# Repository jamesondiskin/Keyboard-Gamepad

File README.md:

# Keyboard-Gamepad
 MX Switch based gamepad for fighting games

Added way too many submodules as for now I am unsure which parts library to use.

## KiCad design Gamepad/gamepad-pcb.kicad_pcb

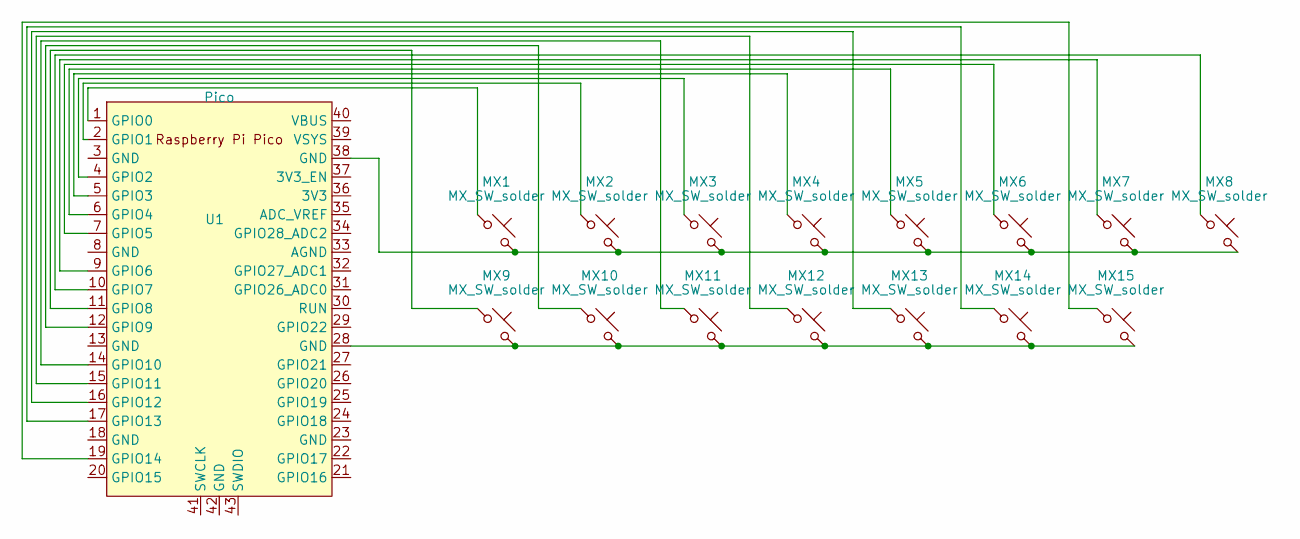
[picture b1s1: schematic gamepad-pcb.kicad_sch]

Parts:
MX1, MX2, MX3, MX4, MX5, MX6, MX7, MX8, MX9, MX10, MX11, MX12, MX13, MX14, MX15: MX_SW_solder; SW_MX_1u
U1: Pico; RPi_Pico_SMD_TH

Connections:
unnamed: MX1.2, MX2.2, MX3.2, MX4.2, MX5.2, MX6.2, MX7.2, MX8.2, U1.38 (GND)
unnamed: MX9.2, MX10.2, MX11.2, MX12.2, MX13.2, MX14.2, MX15.2, U1.28 (GND)
unnamed: MX1.1, U1.1 (GPIO0)
unnamed: MX2.1, U1.2 (GPIO1)
unnamed: MX3.1, U1.4 (GPIO2)
unnamed: MX4.1, U1.5 (GPIO3)
unnamed: MX5.1, U1.6 (GPIO4)
unnamed: MX6.1, U1.7 (GPIO5)
unnamed: MX7.1, U1.9 (GPIO6)
unnamed: MX8.1, U1.10 (GPIO7)
unnamed: MX9.1, U1.11 (GPIO8)
unnamed: MX10.1, U1.12 (GPIO9)
unnamed: MX11.1, U1.14 (GPIO10)
unnamed: MX12.1, U1.15 (GPIO11)
unnamed: MX13.1, U1.16 (GPIO12)
unnamed: MX14.1, U1.17 (GPIO13)
unnamed: MX15.1, U1.19 (GPIO14)

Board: 2 copper layers, 16 parts (0 on the bottom side), 17 nets, no tracks yet.

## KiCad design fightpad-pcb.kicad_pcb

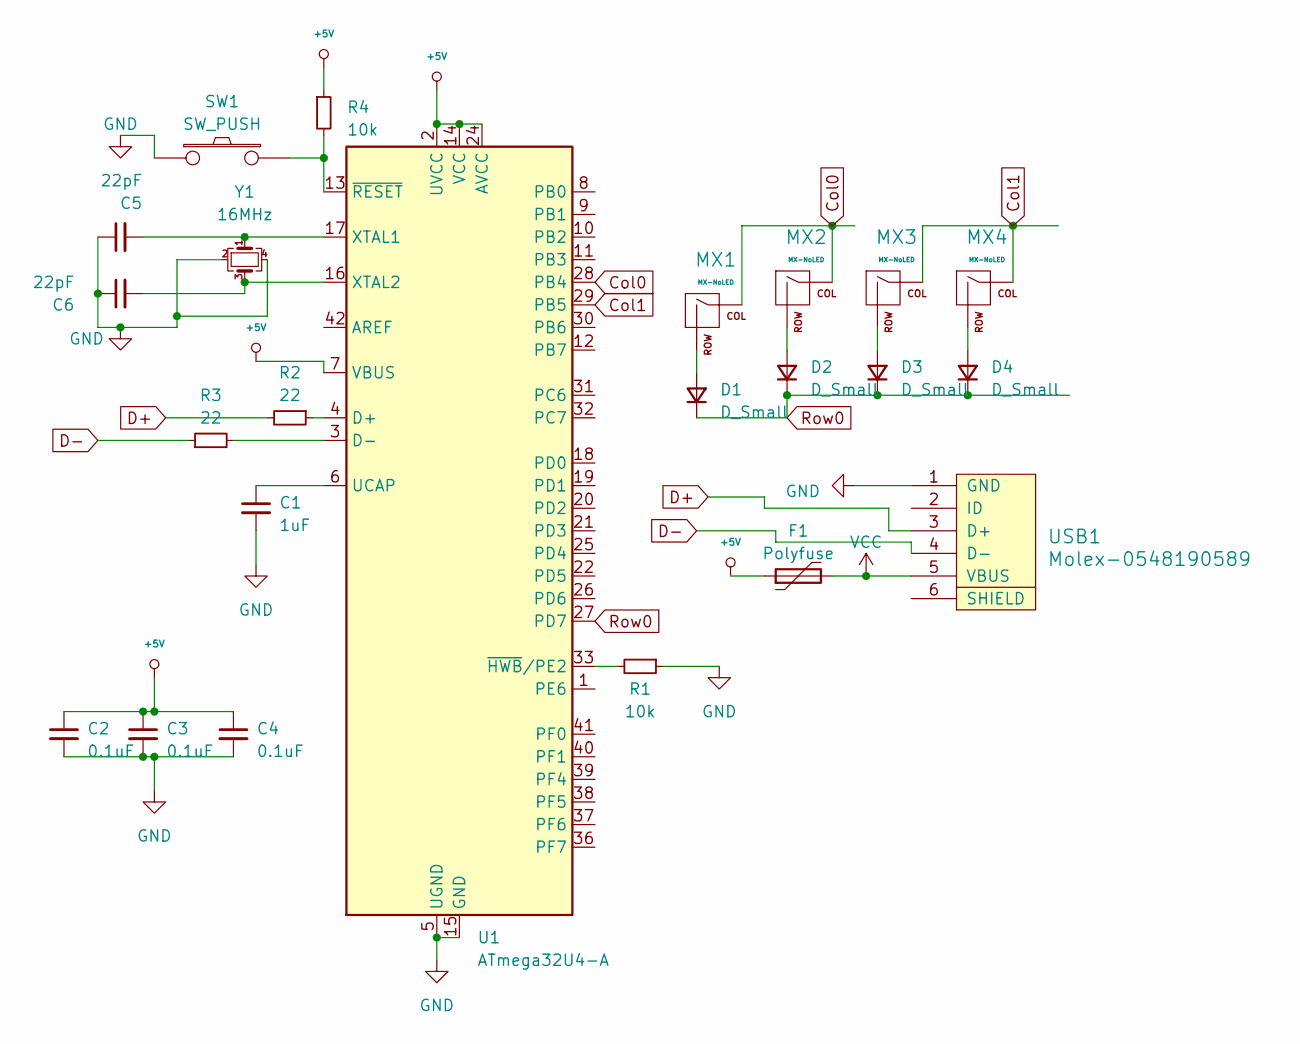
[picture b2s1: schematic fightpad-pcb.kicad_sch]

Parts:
C1: 1uF; C_0805_2012Metric
C2, C3, C4: 0.1uF; C_0805_2012Metric
C5, C6: 22pF; C_0805_2012Metric
D1, D2, D3, D4: D_Small; D_SOD-123
F1: Polyfuse; Fuse_1206_3216Metric
MX1, MX2, MX3, MX4: MX-NoLED; MX-1U
R1, R4: 10k; R_0805_2012Metric
R2, R3: 22; R_0805_2012Metric
SW1: SW_PUSH; SKQG-1155865
U1: ATmega32U4-A; TQFP-44_10x10mm_P0.8mm
USB1: Molex-0548190589
Y1: 16MHz; Crystal_SMD_3225-4Pin_3.2x2.5mm

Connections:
+5V: C2.1, C3.1, C4.1, F1.1, R4.1, U1.2 (UVCC), U1.7 (VBUS), U1.14 (VCC), U1.24 (AVCC), U1.34 (VCC), U1.44 (AVCC)
Col0: MX1.1 (COL), MX2.1 (COL), U1.28 (PB4)
Col1: MX3.1 (COL), MX4.1 (COL), U1.29 (PB5)
D+: R2.2, USB1.3 (D+)
D-: R3.1, USB1.4 (D-)
GND: C1.2, C2.2, C3.2, C4.2, C5.1, C6.1, R1.1, SW1.1, U1.5 (UGND), U1.15 (GND), U1.23 (GND), U1.35 (GND), U1.43 (GND), USB1.1 (GND), Y1.2, Y1.4
unnamed: D1.2 (A), MX1.2 (ROW)
unnamed: D2.2 (A), MX2.2 (ROW)
unnamed: D3.2 (A), MX3.2 (ROW)
unnamed: D4.2 (A), MX4.2 (ROW)
unnamed: R2.1, U1.4 (D+)
unnamed: R3.2, U1.3 (D-)
unnamed: C1.1, U1.6 (UCAP)
unnamed: C5.2, U1.17 (XTAL1), Y1.1
unnamed: C6.2, U1.16 (XTAL2), Y1.3
unnamed: R1.2, U1.33 (~HWB/PE2)
unnamed: R4.2, SW1.2, U1.13 (~RESET)
Row0: D1.1 (K), D2.1 (K), D3.1 (K), D4.1 (K), U1.27 (PD7)
VCC: F1.2, USB1.5 (VBUS)

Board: 2 copper layers, 23 parts (0 on the bottom side), 19 nets, no tracks yet.

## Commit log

2023-07-29 Initial File Creation
2023-07-29 Add submodules
2023-07-29 Added libraries
    Added several libraries from ramdom-keyboard-parts.pretty, MX_ALps_Hybrid.pretty, and more to both Schematic and PCB Editor
2023-07-29 MCU Schematic
    Following along with ai03's guide (https://wiki.ai03.com/books/pcb-design/page/pcb-guide-part-3---creating-the-mcu-schematic) the MCU Schematic has been assembled
2023-07-29 Schematic Finished
    Schematic finished with slight modifications. Further changes to be made, but this is the base version
2023-07-29 Reorganization
    Prep for Pro Micro Based File after Test File Finished
2023-07-29 Add ProMicro Submodule
2023-07-29 More switch libraries to experiment with
2023-07-29 v1 Complete
2023-07-30 Finals removed, prototype one files created.
